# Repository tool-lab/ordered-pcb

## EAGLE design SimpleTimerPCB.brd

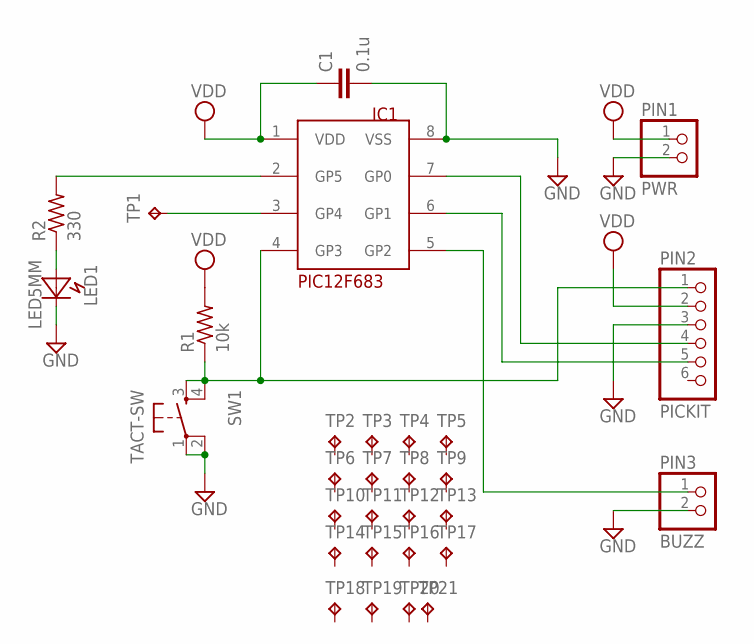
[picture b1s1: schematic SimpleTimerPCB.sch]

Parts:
C1: 0.1u; C025-024X044
LED1: LED5MM; LED_5MM
PIC12F683: IC1; DIL08
PIN1: PWR; 1X02
PIN2: PICKIT; 1X06
PIN3: BUZZ; 1X02
R1: 10k; 0207/10
R2: 330; 0207/10
SW1: TACT-SW; B3F-10X
TP1: TPPAD1-17; P1-17
TP2, TP3, TP4, TP5, TP6, TP7, TP8, TP9, TP10, TP11, TP12, TP13, TP14, TP15, TP16, TP17, TP18, TP19, TP20, TP21: TPNORMAL; TPAD-NORM

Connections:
GND: C1.2, LED1.K, PIC12F683.8 (VSS), PIN1.2, PIN2.3, PIN3.2, SW1.1, SW1.2 (P1)
unnamed: PIC12F683.4 (GP3), PIN2.1, R1.1, SW1.3 (S), SW1.4 (S1)
unnamed: PIC12F683.3 (GP4), TP1.TP
unnamed: PIC12F683.7 (GP0), PIN2.4
unnamed: PIC12F683.6 (GP1), PIN2.5
unnamed: PIC12F683.5 (GP2), PIN3.1
unnamed: LED1.A, R2.1
unnamed: PIC12F683.2 (GP5), R2.2
VDD: C1.1, PIC12F683.1 (VDD), PIN1.1, PIN2.2, R1.2

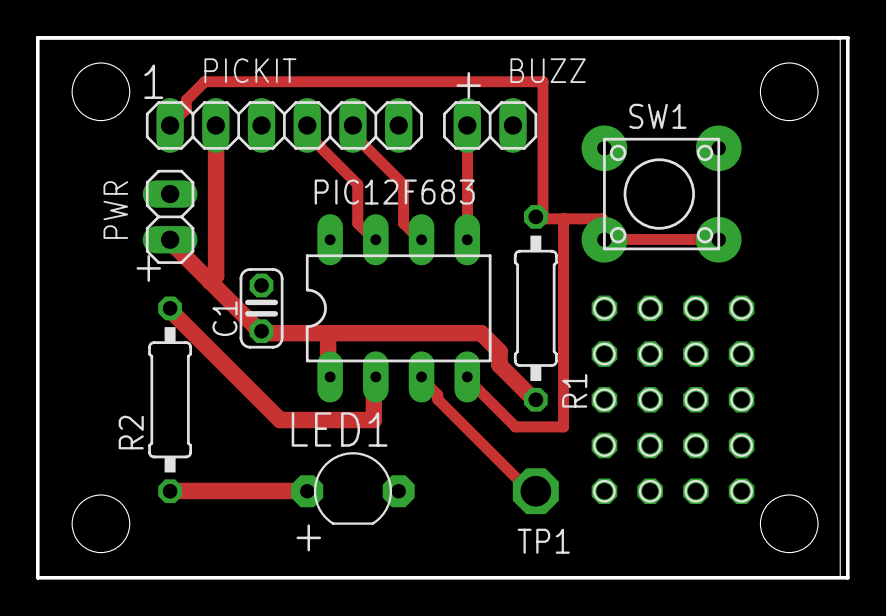
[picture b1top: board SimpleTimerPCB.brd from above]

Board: 2 copper layers, 45.0 x 30.0 mm, 30 parts (0 on the bottom side), 9 nets.
